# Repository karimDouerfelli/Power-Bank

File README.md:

the english version is after 

# 🔋 Powerbank 10 000 mAh – Guide Complet PCB (Version 2 × Cellules 1S)

## 1. 📖 L’histoire

On veut fabriquer une **batterie externe** qui :

* Se recharge en USB-C
* Peut charger un téléphone vite (QC/PD)
* A une capacité \~**10 000 mAh**
* Utilise **2 cellules 1S** (en parallèle = 1S2P)

---

## 2. 🧠 Comment ça marche

Imagine deux bouteilles d’eau identiques (les **cellules**).
Si on les relie en parallèle, c’est comme verser dans une grande bassine : plus de capacité mais **même tension**.
Ensuite, un **cerveau électronique** (le BMS et le chip de gestion USB) contrôle :

* **La charge** (ne pas dépasser la tension max)
* **La décharge** (ne pas descendre trop bas)
* **La température** (ne pas chauffer)

---

## 3. 📦 Les ingrédients (BOM principale)

| Nom du composant                | Rôle                                                          | Référence conseillée               |
| ------------------------------- | ------------------------------------------------------------- | ---------------------------------- |
| **Contrôleur USB-C tout-en-un** | Gérer charge/décharge USB, QC, PD                             | IP5328P                            |
| **BMS 1S**                      | Protéger la batterie (surcharge, court-circuit, sous-tension) | DW01A + FS8205A                    |
| **MOSFETs**                     | Couper ou autoriser le courant                                | FS8205A (dans le BMS)              |
| **Cellules Li-ion**             | Source d’énergie                                              | 2× Samsung INR21700-50E (5000 mAh) |
| **NTC 10 kΩ**                   | Mesurer température                                           | 103AT-2                            |
| **PTC (Polyfuse)**              | Protection contre surcourant                                  | RUE600-0.5                         |
| **Condensateurs céramiques**    | Lisser le courant                                             | 10 µF et 22 µF X5R/X7R             |
| **Résistances de détection**    | Mesurer courant/tension                                       | Shunt 10–20 mΩ                     |
| **Connecteur USB-C**            | Entrée/sortie énergie                                         | Type-C réversible                  |
| **PCB 4 couches**               | Support et connexions                                         | 100×60 mm, 1 oz cuivre             |

---

## 4. 🛠 Schéma de principe

```
[Cellule 1]---+
              |---(Pont de mise en parallèle)---[VBAT]---[BMS 1S]---[IP5328P]---USB-C
[Cellule 2]---+

[NTC] -> vers IP5328P
[PTC] -> sur ligne VBAT après les cellules
```

* **Cellule 1** et **Cellule 2** sont reliées **en parallèle** via un pont (peut être un jumper ou une résistance d’équilibrage temporaire).
* **VBAT** = point où la tension batterie arrive sur le PCB.
* **BMS 1S** placé **avant** le contrôleur USB pour protéger la batterie.

---

## 5. 🎨 Design du PCB (4 couches)

**Couche 1 (Top)**

* Composants principaux (IP5328P, BMS, USB-C)
* Pistes de signal
* Zones de cuivre pour le **+BAT** et **GND**
* Largeur piste batterie : ≥ 2 mm (pour 3–5 A)

**Couche 2 (GND)**

* Plan de masse complet (GND)
* Connexions directes aux pads GND des composants

**Couche 3 (VBAT)**

* Plan entier pour le +BAT (après BMS)
* Évite pertes et échauffement

**Couche 4 (Bottom)**

* Composants secondaires (résistances, petits condos)
* Pads pour test (VBAT\_A, VBAT\_B, VBAT\_SUM)
* Pont de mise en parallèle (empreinte de résistance/jumper)

---

## 6. 🧩 Étapes de routage

1. **Commencer par le connecteur USB-C**

   * Traces différentielles pour CC1/CC2 si besoin
   * Pistes larges pour VBUS et GND
2. **Placer l’IP5328P** proche du port USB-C

   * Condensateurs d’entrée/sortie **le plus près possible**
3. **BMS 1S** proche des pads BAT+ / BAT-

   * MOSFETs orientés pour flux direct vers IP5328P
4. **Plans de cuivre** :

   * GND sur Couche 2
   * VBAT sur Couche 3
5. **Pads séparés pour Cellule 1 et Cellule 2**

   * Permet test individuel avant soudure
6. **Pont de mise en parallèle** :

   * Footprint d’une résistance 1206 (0.5–1 Ω)
   * Remplacée par un shunt une fois équilibré
7. **NTC** :

   * Empreinte pour connecteur JST ou soudage direct
   * Placer piste fine vers IP5328P

---

## 7. 🔌 Connexions importantes

* **VBAT\_A** et **VBAT\_B** : chaque cellule séparée
* **Pont parallèle** : à fermer après équilibrage
* **PTC** : en série sur VBAT pour protection
* **NTC** : collée sur cellule et reliée au contrôleur
* **Shunt courant** : entre BMS et IP5328P

---

## 8. 📐 Règles de fabrication PCB

* **Épaisseur cuivre** : 1 oz (35 µm)
* **Largeur piste puissance** : ≥ 2 mm pour >3 A
* **Via stitching** sur zones VBAT et GND
* **Minimum clearance** : 0.2 mm
* **Sérigraphie** claire (polarités, repères tests)

---

## 9. 📋 Procédure d’assemblage

1. Souder tous les composants CMS du PCB
2. Fixer connecteur USB-C
3. Relier cellules **sans** fermer le pont parallèle
4. Mesurer tension des deux cellules

   * Si écart ≤ 0.05 V → fermer pont (shunt)
5. Fixer NTC sur cellule
6. Brancher batterie et tester charge/décharge
7. Si tout OK → fermer boîtier

---

## 10. 💰 Coût estimatif

| Élément                  | Prix (\~€) |
| ------------------------ | ---------- |
| IP5328P                  | 0.90       |
| BMS 1S                   | 0.40       |
| MOSFETs supplémentaires  | 0.20       |
| USB-C                    | 0.30       |
| Passifs (résistances, C) | 1.50       |
| PCB 4 couches            | 3.00       |
| Cellules Li-ion          | 6.90       |
| **Total**                | **\~16.8** |

---

## 11. ⚠ Conseils sécurité

* Ne jamais court-circuiter une cellule
* Toujours vérifier température lors des premiers cycles
* Utiliser uniquement cellules en bon état et identiques

---

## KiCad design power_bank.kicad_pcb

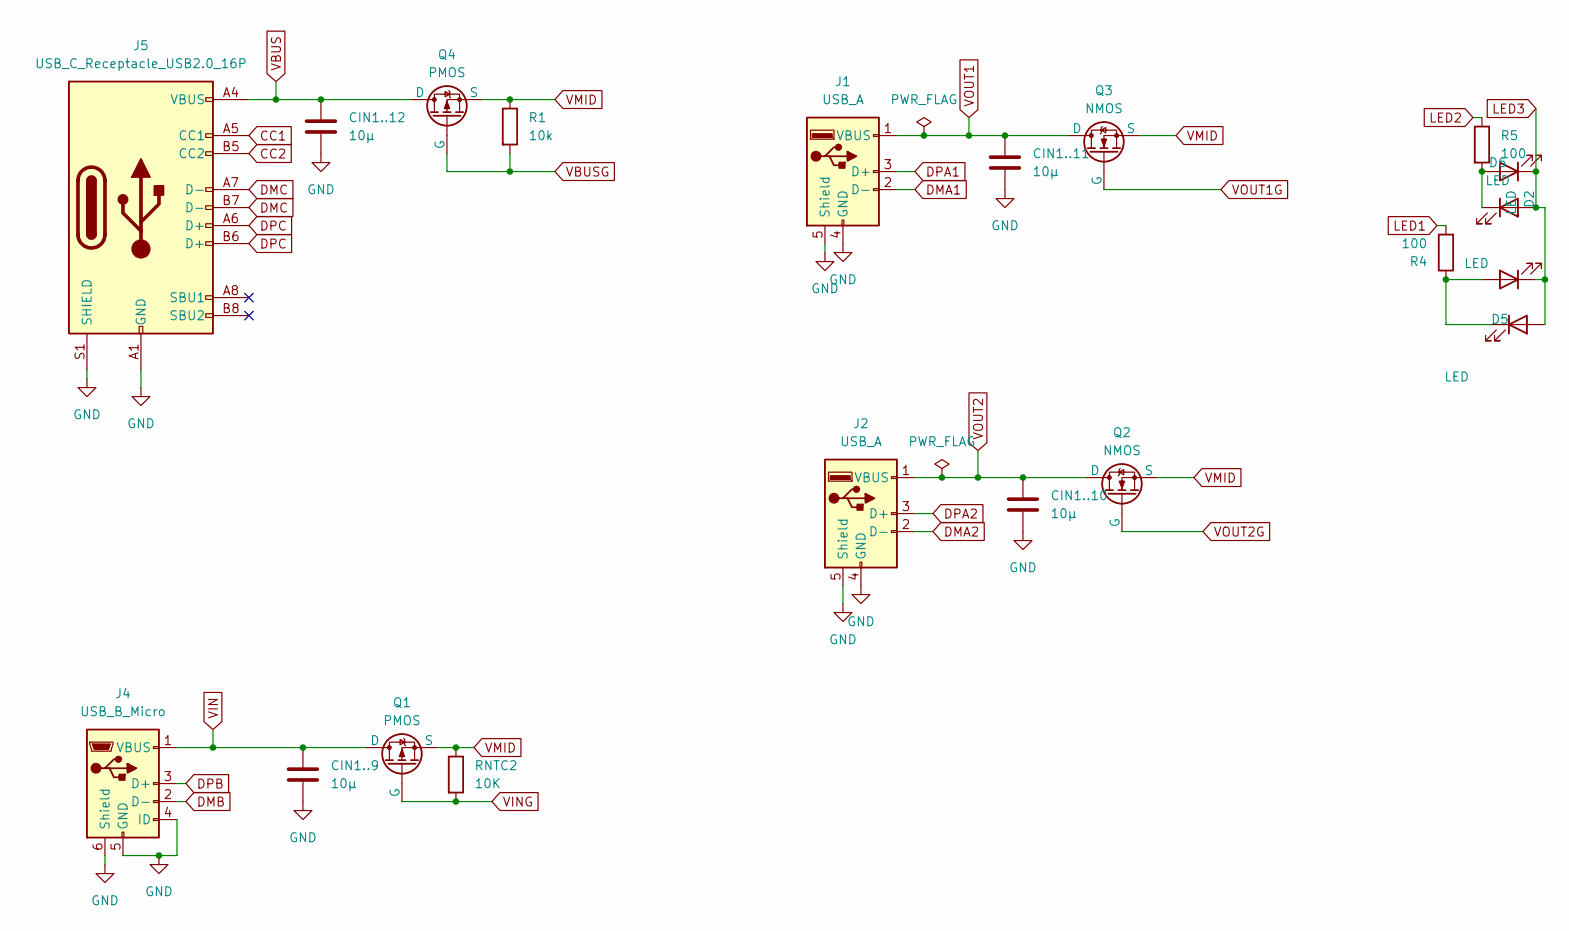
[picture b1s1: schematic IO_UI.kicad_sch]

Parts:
CIN1..9, CIN1..10, CIN1..11, CIN1..12: 10µ; C_0805_2012Metric
D1, D2, D5, D6: LED; LED_0603_1608Metric
J1, J2: USB_A; USB_A_CNCTech_1001-011-01101_Horizontal
J4: USB_B_Micro; USB_Micro-B_Wuerth_629105150521
J5: USB_C_Receptacle_USB2.0_16P; USB_C_Receptacle_HCTL_HC-TYPE-C-16P-01A
Q1, Q4: PMOS; TSOT-23
Q2, Q3: NMOS; TSOT-23
R1: 10k; R_0603_1608Metric
R4, R5: 100; R_0603_1608Metric
RNTC2: 10K; R_0603_1608Metric

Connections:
CC1: J5.A5 (CC1); also elsewhere on the board
CC2: J5.B5 (CC2); also elsewhere on the board
DMA1: J1.2 (D-); also elsewhere on the board
DMA2: J2.2 (D-); also elsewhere on the board
DMB: J4.2 (D-); also elsewhere on the board
DMC: J5.A7 (D-), J5.B7 (D-); also elsewhere on the board
DPA1: J1.3 (D+); also elsewhere on the board
DPA2: J2.3 (D+); also elsewhere on the board
DPB: J4.3 (D+); also elsewhere on the board
DPC: J5.A6 (D+), J5.B6 (D+); also elsewhere on the board
GND: CIN1..9.2, CIN1..10.2, CIN1..11.2, CIN1..12.2, J1.4 (GND), J1.5 (Shield), J2.4 (GND), J2.5 (Shield), J4.4 (ID), J4.5 (GND), J4.6 (Shield), J5.A1 (GND), J5.A12 (GND), J5.B1 (GND), J5.B12 (GND), J5.S1 (SHIELD); also elsewhere on the board
LED1: R4.2; also elsewhere on the board
LED2: R5.1; also elsewhere on the board
LED3: D1.1 (K), D2.1 (K), D5.2 (A), D6.2 (A); also elsewhere on the board
unnamed: D1.2 (A), D5.1 (K), R4.1
unnamed: D2.2 (A), D6.1 (K), R5.2
VBUS: CIN1..12.1, J5.A4 (VBUS), J5.A9 (VBUS), J5.B4 (VBUS), J5.B9 (VBUS), Q4.1 (D); also elsewhere on the board
VBUSG: Q4.2 (G), R1.2; also elsewhere on the board
VIN: CIN1..9.1, J4.1 (VBUS), Q1.1 (D); also elsewhere on the board
VING: Q1.2 (G), RNTC2.2; also elsewhere on the board
VMID: Q1.3 (S), Q2.3 (S), Q3.3 (S), Q4.3 (S), R1.1, RNTC2.1; also elsewhere on the board
VOUT1: CIN1..11.1, J1.1 (VBUS), Q3.1 (D); also elsewhere on the board
VOUT1G: Q3.2 (G); also elsewhere on the board
VOUT2: CIN1..10.1, J2.1 (VBUS), Q2.1 (D); also elsewhere on the board
VOUT2G: Q2.2 (G); also elsewhere on the board

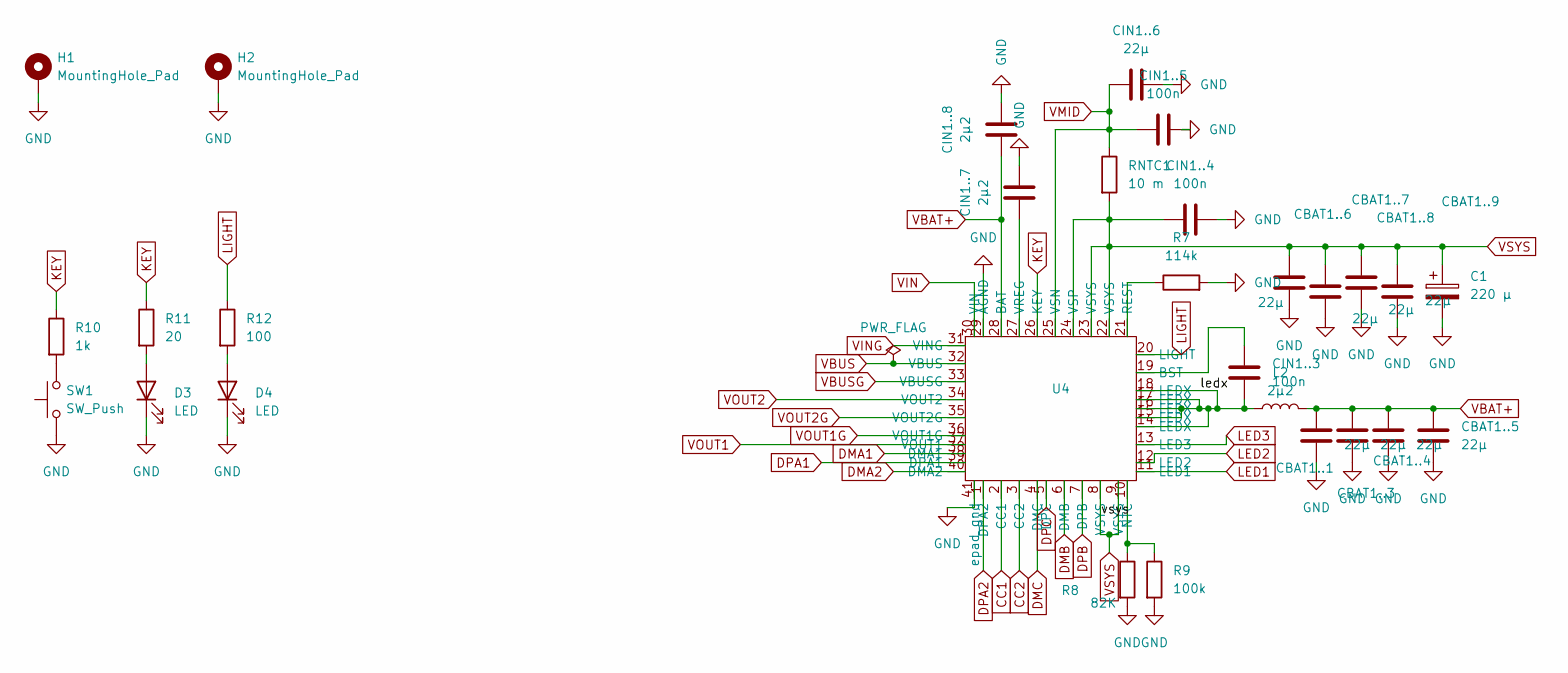
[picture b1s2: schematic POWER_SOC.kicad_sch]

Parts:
C1: 220 µ; CAPPRD500W60D1000H2500
CBAT1..1, CBAT1..3, CBAT1..4, CBAT1..5, CBAT1..6, CBAT1..7, CBAT1..8, CBAT1..9: 22µ; C_0805_2012Metric
CIN1..3, CIN1..4, CIN1..5: 100n; C_0603_1608Metric
CIN1..6: 22µ; C_0805_2012Metric
CIN1..7, CIN1..8: 2µ2; C_0603_1608Metric
D3: LED; LED_D3.0mm
D4: LED; LED_0603_1608Metric
H1, H2: MountingHole_Pad; MountingHole_2.2mm_M2_DIN965_Pad
L2: 2µ2; L_10.4x10.4_H4.8
R7: 114k; R_0603_1608Metric
R8: 82K; R_0603_1608Metric
R9: 100k; R_0603_1608Metric
R10: 1k; R_0603_1608Metric
R11: 20; R_0603_1608Metric
R12: 100; R_0603_1608Metric
RNTC1: 10 m; R_1206_3216Metric
SW1: SW_Push; SW_DIP_SPSTx01_Slide_6.7x4.1mm_W6.73mm_P2.54mm_LowProfile_J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
U4: QFN-40-1EP_6x6mm_P0.5mm_EP4.6x4.6mm

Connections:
/POWER_SOC/ledx: CIN1..3.1, L2.1, U4.14 (LEDX), U4.15 (LEDX), U4.16 (LEDX), U4.17 (LEDX), U4.18 (LEDX)
CC1: U4.2 (CC1); also elsewhere on the board
CC2: U4.3 (CC2); also elsewhere on the board
DMA1: U4.38 (DMA1); also elsewhere on the board
DMA2: U4.40 (DMA2); also elsewhere on the board
DMB: U4.6 (DMB); also elsewhere on the board
DMC: U4.4 (DMC); also elsewhere on the board
DPA1: U4.39 (DPA1); also elsewhere on the board
DPA2: U4.1 (DPA2); also elsewhere on the board
DPB: U4.7 (DPB); also elsewhere on the board
DPC: U4.5 (DPC); also elsewhere on the board
GND: C1.2, CBAT1..1.2, CBAT1..3.2, CBAT1..4.2, CBAT1..5.2, CBAT1..6.2, CBAT1..7.2, CBAT1..8.2, CBAT1..9.2, CIN1..4.1, CIN1..5.1, CIN1..6.1, CIN1..7.1, CIN1..8.1, D3.1 (K), D4.1 (K), H1.1, H2.1, R7.2, R8.2, R9.2, SW1.1, U4.29 (AGND), U4.41 (epad_gnd); also elsewhere on the board
KEY: R10.1, R11.1, U4.26 (KEY)
LED1: U4.11 (LED1); also elsewhere on the board
LED2: U4.12 (LED2); also elsewhere on the board
LED3: U4.13 (LED3); also elsewhere on the board
LIGHT: R12.1, U4.20 (LIGHT)
unnamed: D3.2 (A), R11.2
unnamed: D4.2 (A), R12.2
unnamed: R10.2, SW1.2
unnamed: CIN1..3.2, U4.19 (BST)
unnamed: R8.1, R9.1, U4.10 (NTC)
unnamed: R7.1, U4.21 (REST)
unnamed: CIN1..7.2, U4.27 (VREG)
VBAT+: CBAT1..1.1, CBAT1..3.1, CBAT1..4.1, CBAT1..5.1, CIN1..8.2, L2.2, U4.28 (BAT)
VBUS: U4.32 (VBUS); also elsewhere on the board
VBUSG: U4.33 (VBUSG); also elsewhere on the board
VIN: U4.30 (VIN); also elsewhere on the board
VING: U4.31 (VING); also elsewhere on the board
VMID: CIN1..5.2, CIN1..6.2, RNTC1.1, U4.25 (VSN); also elsewhere on the board
VOUT1: U4.37 (VOUT1); also elsewhere on the board
VOUT1G: U4.36 (VOUT1G); also elsewhere on the board
VOUT2: U4.34 (VOUT2); also elsewhere on the board
VOUT2G: U4.35 (VOUT2G); also elsewhere on the board
VSYS: C1.1, CBAT1..6.1, CBAT1..7.1, CBAT1..8.1, CBAT1..9.1, CIN1..4.2, RNTC1.2, U4.8 (VSYS), U4.9 (VSYS), U4.22 (VSYS), U4.23 (VSYS), U4.24 (VSP)

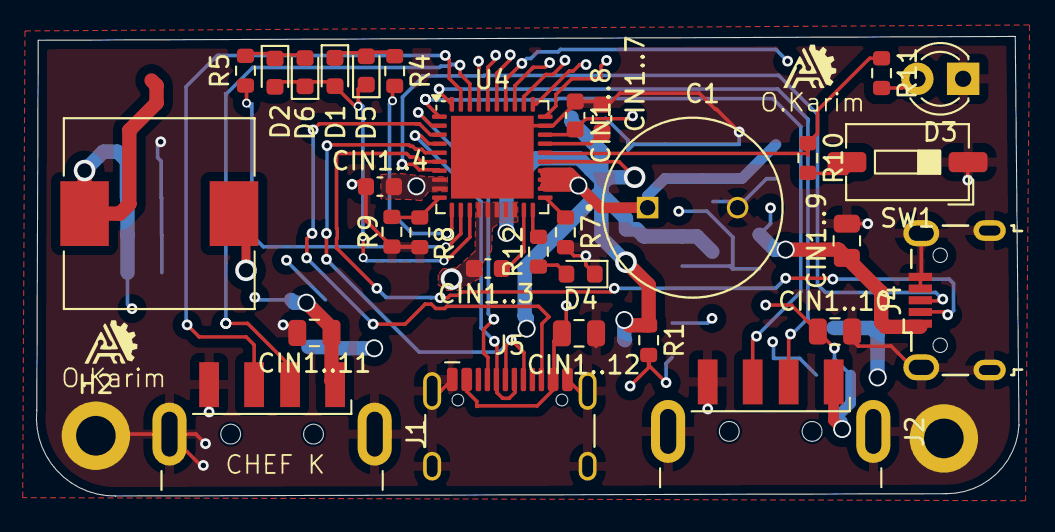
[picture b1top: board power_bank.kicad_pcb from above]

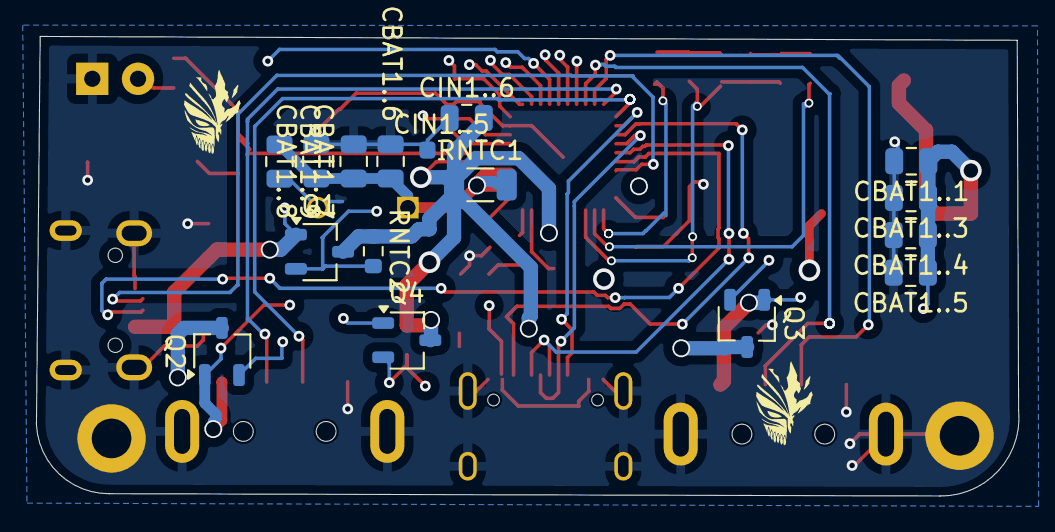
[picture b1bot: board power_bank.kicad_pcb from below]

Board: 4 copper layers, 54.6 x 25.5 mm, 49 parts (16 on the bottom side), 37 nets.

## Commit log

2025-09-25 Premier commit
2025-10-10 gerber command
